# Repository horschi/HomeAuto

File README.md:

# HomeAuto
Home automation - reads EBus data from my Hautec heat pump (TEM controller) and sets the speed of the ventilation

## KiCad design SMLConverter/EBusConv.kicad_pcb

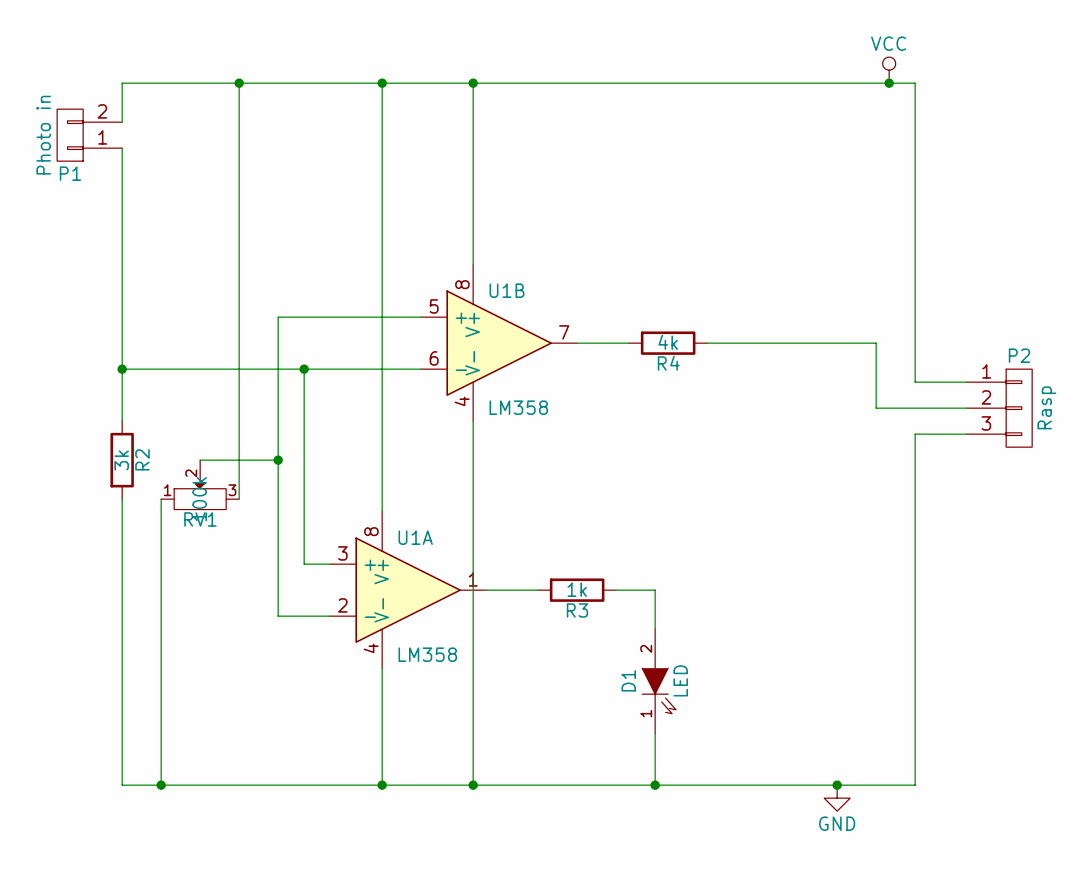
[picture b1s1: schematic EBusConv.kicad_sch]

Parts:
D1: LED; LED-5MM
P1: Photo in; Pin_Header_Straight_1x02
P2: Rasp; Socket_Strip_Straight_1x03
R2: 3k; Resistor_Horizontal_RM10mm
R3: 1k; Resistor_Horizontal_RM10mm
R4: 4k; Resistor_Horizontal_RM10mm
RV1: 100k; Potentiometer_Trimmer-Piher_PT15-V15_horizontal
U1: LM358; DIP-8_W7.62mm

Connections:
GND: D1.1 (K), P2.3, R2.2, RV1.1, U1.4 (V-)
unnamed: D1.2 (A), R3.1
unnamed: P1.1, R2.1, U1.3 (+), U1.6 (-)
unnamed: P2.2, R4.1
unnamed: R3.2, U1.1
unnamed: R4.2, U1.7
unnamed: RV1.2, U1.2 (-), U1.5 (+)
VCC: P1.2, P2.1, RV1.3, U1.8 (V+)

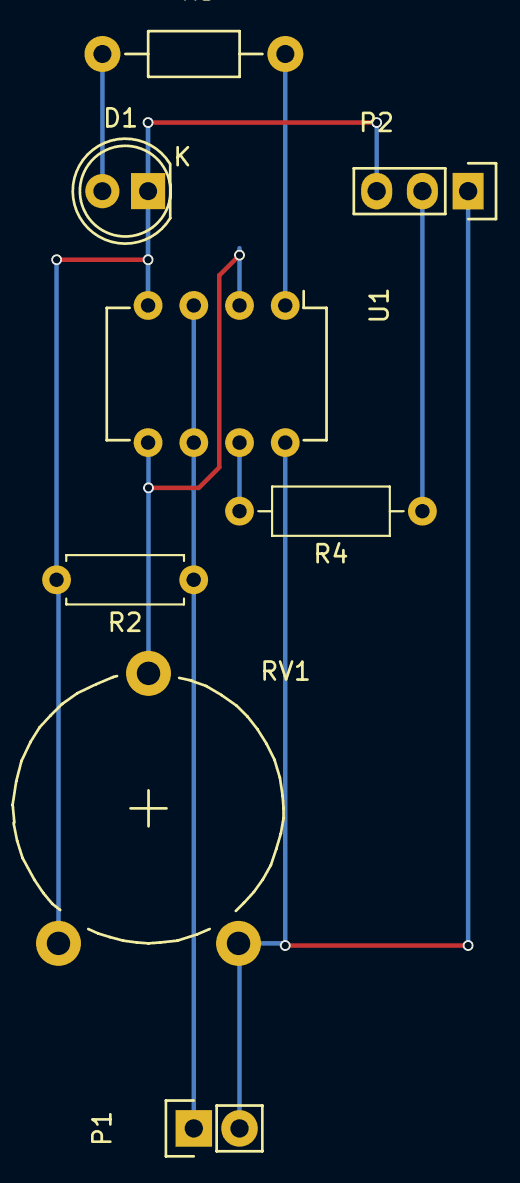
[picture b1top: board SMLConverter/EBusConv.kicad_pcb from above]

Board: 2 copper layers, 8 parts (0 on the bottom side), 8 nets.

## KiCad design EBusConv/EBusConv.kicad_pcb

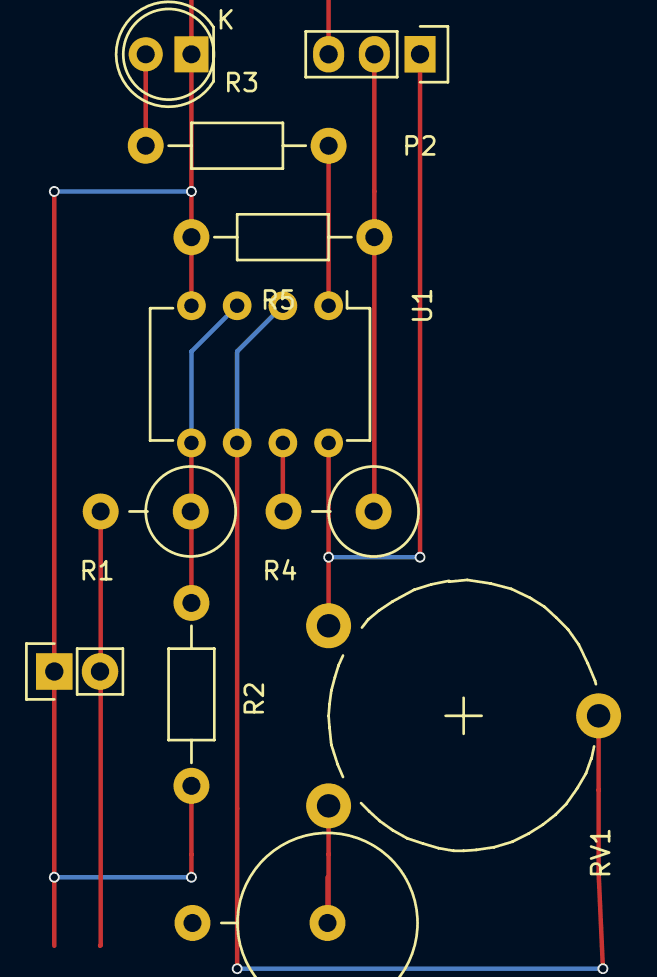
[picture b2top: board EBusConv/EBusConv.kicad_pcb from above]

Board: 2 copper layers, 11 parts (0 on the bottom side), 10 nets.

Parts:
D1: LED; LED-5MM
P1: EBus in; Pin_Header_Straight_1x02
P2: Rasp; Socket_Strip_Straight_1x03
R1: 30k; Resistor_Vertical_RM5mm
R2: 3k; Resistor_Horizontal_RM10mm
R3: 1k; Resistor_Horizontal_RM10mm
R4: 4k; Resistor_Vertical_RM5mm
R5: 40k; Resistor_Horizontal_RM10mm
R6: 10k; Resistor_Vertical_RM7.5mm
RV1: 100k; Potentiometer_Trimmer-Piher_PT15-V15_horizontal
U1: LM358; DIP-8_W7.62mm

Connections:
GND: D1.1, P1.1, P2.3, R2.2, R5.2, R6.2, U1.4
unnamed: D1.2, R3.1
unnamed: P1.2, R1.2
unnamed: P2.2, R4.1, R5.1
unnamed: R1.1, R2.1, U1.3, U1.5
unnamed: R3.2, U1.1
unnamed: R4.2, U1.7
unnamed: R6.1, RV1.3
unnamed: RV1.2, U1.2, U1.6
VCC: P2.1, RV1.1, U1.8

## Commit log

2017-12-15 git ignore
2017-12-16 refactoring, timings for known values
2017-12-16 fixed copy&paste
2017-12-23 cleanup
2017-12-24 UI tweaks, more params, cleanup
2017-12-27 rounding, UI, fixed params, vent default value
2018-09-30 schedules
2021-10-28 refactoring, alternative serial api
2021-10-29 refactoring
2021-10-30 made configurable
2021-10-30 protocol
2021-10-31 vent commands
2021-10-31 cmd fixes
2021-11-01 more commands
2021-11-04 commands
2021-11-07 serial test
2021-11-07 cleanup, fixes, new commands
2021-11-13 SML parser
2021-11-14 SML parsing
2021-11-21 logging
2021-11-28 meter label
2021-12-11 CRC16 check, value format
2021-12-11 various fixes
2021-12-11 data sending
2021-12-12 value sending
2021-12-12 sending fixes
2021-12-31 cleanup, internet connection test
2021-12-31 schedule saving
2021-12-31 value history, internet ping
2021-12-31 conntest
2022-01-11 fixes
2022-01-11 conn check
2022-01-29 value delete
2022-02-13 tagesverbrauch
2022-04-18 debug statistics
2022-04-18 fixup! debug statistics
2022-09-29 nfreq
2022-09-29 deps
2022-11-14 Heating time fix
2022-12-19 NPE fix
2024-09-21 lib update, unknown SML labels
2024-09-22 consuption calc
2024-11-01 ui refresh fix
2025-12-27 shelly support
2025-12-27 tweaking
2026-01-12 settings
2026-01-15 shelly opti
